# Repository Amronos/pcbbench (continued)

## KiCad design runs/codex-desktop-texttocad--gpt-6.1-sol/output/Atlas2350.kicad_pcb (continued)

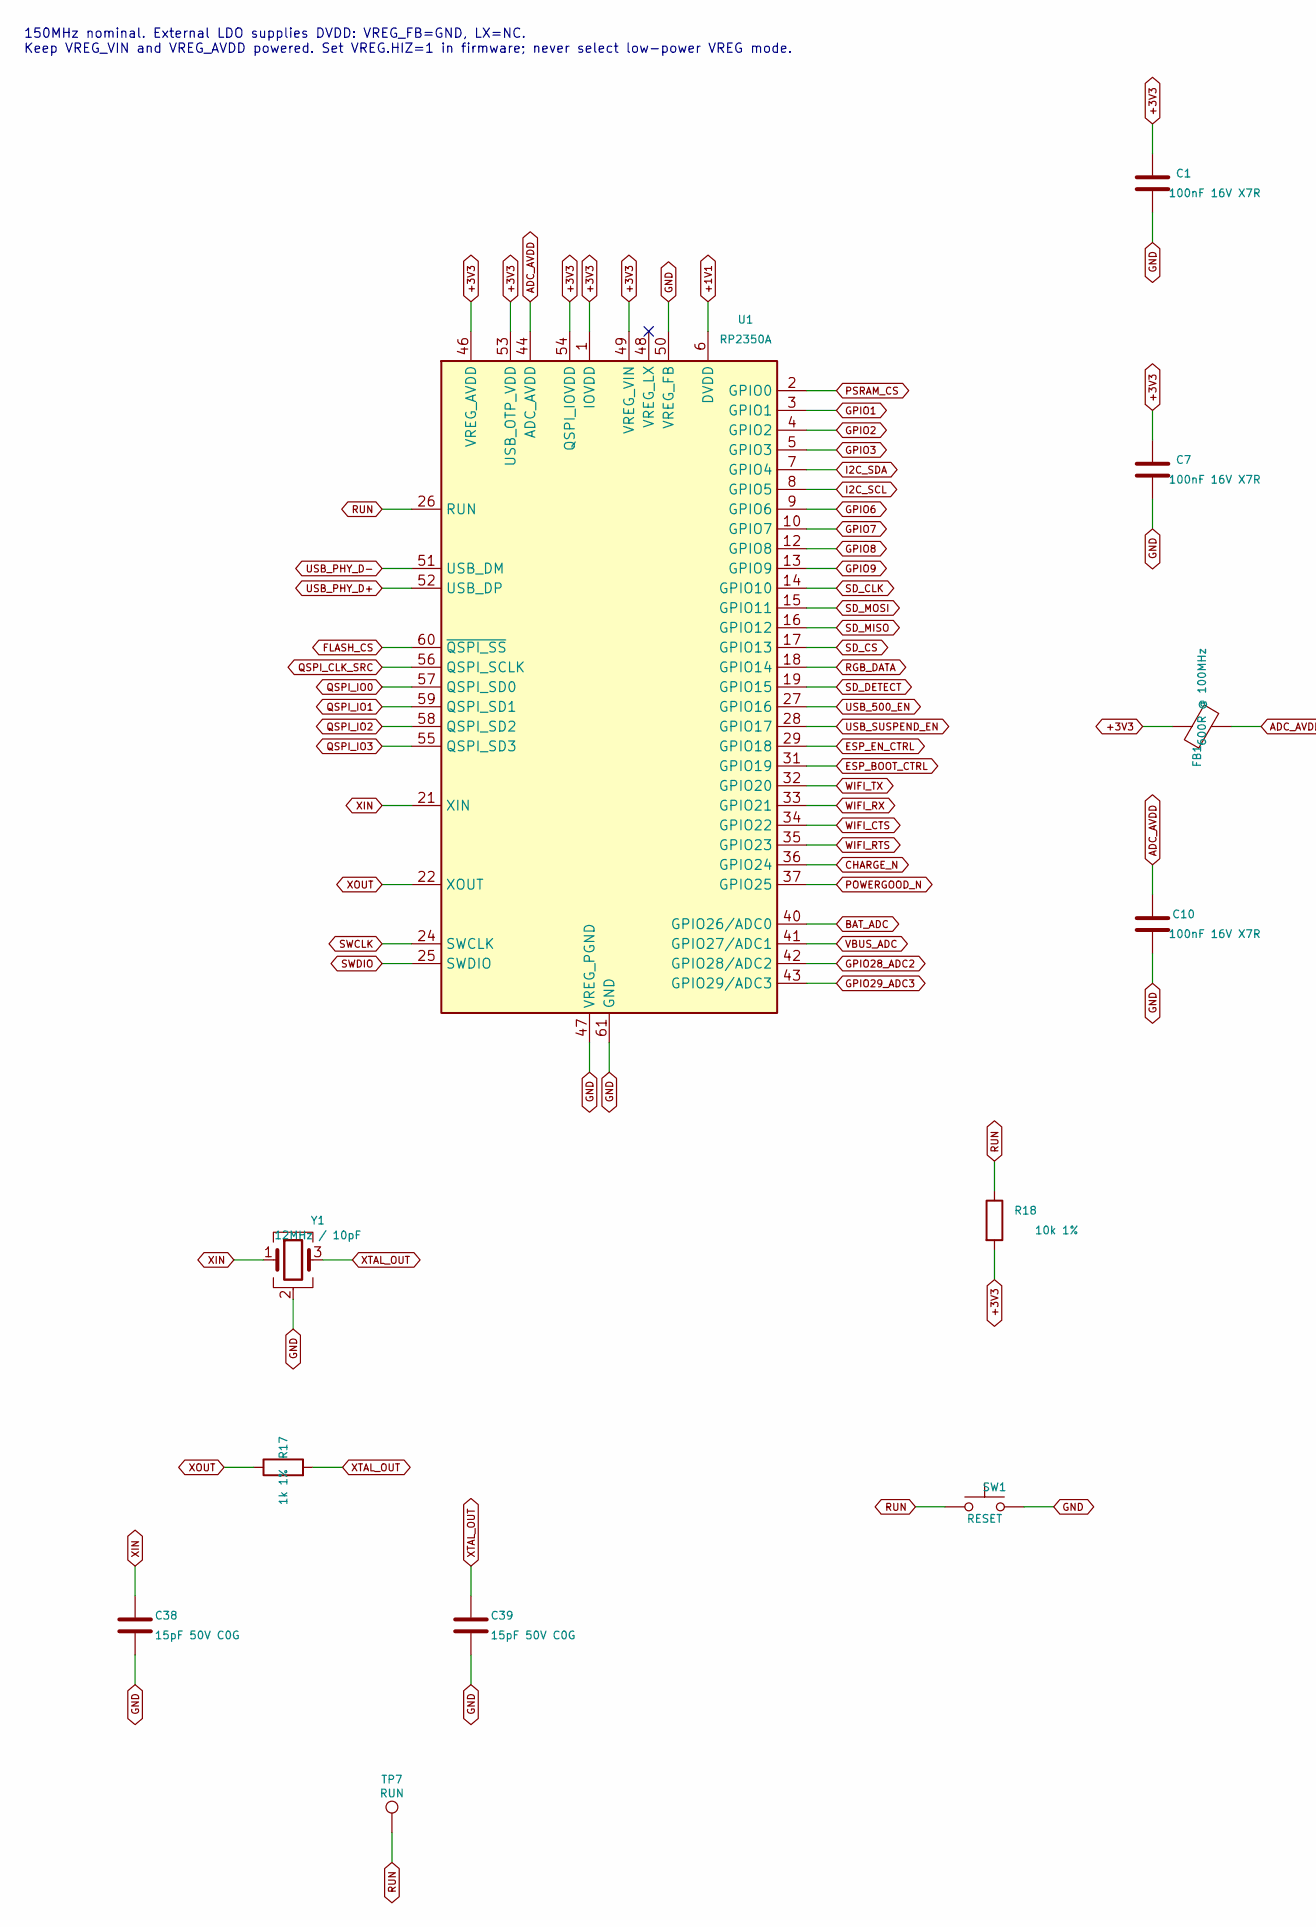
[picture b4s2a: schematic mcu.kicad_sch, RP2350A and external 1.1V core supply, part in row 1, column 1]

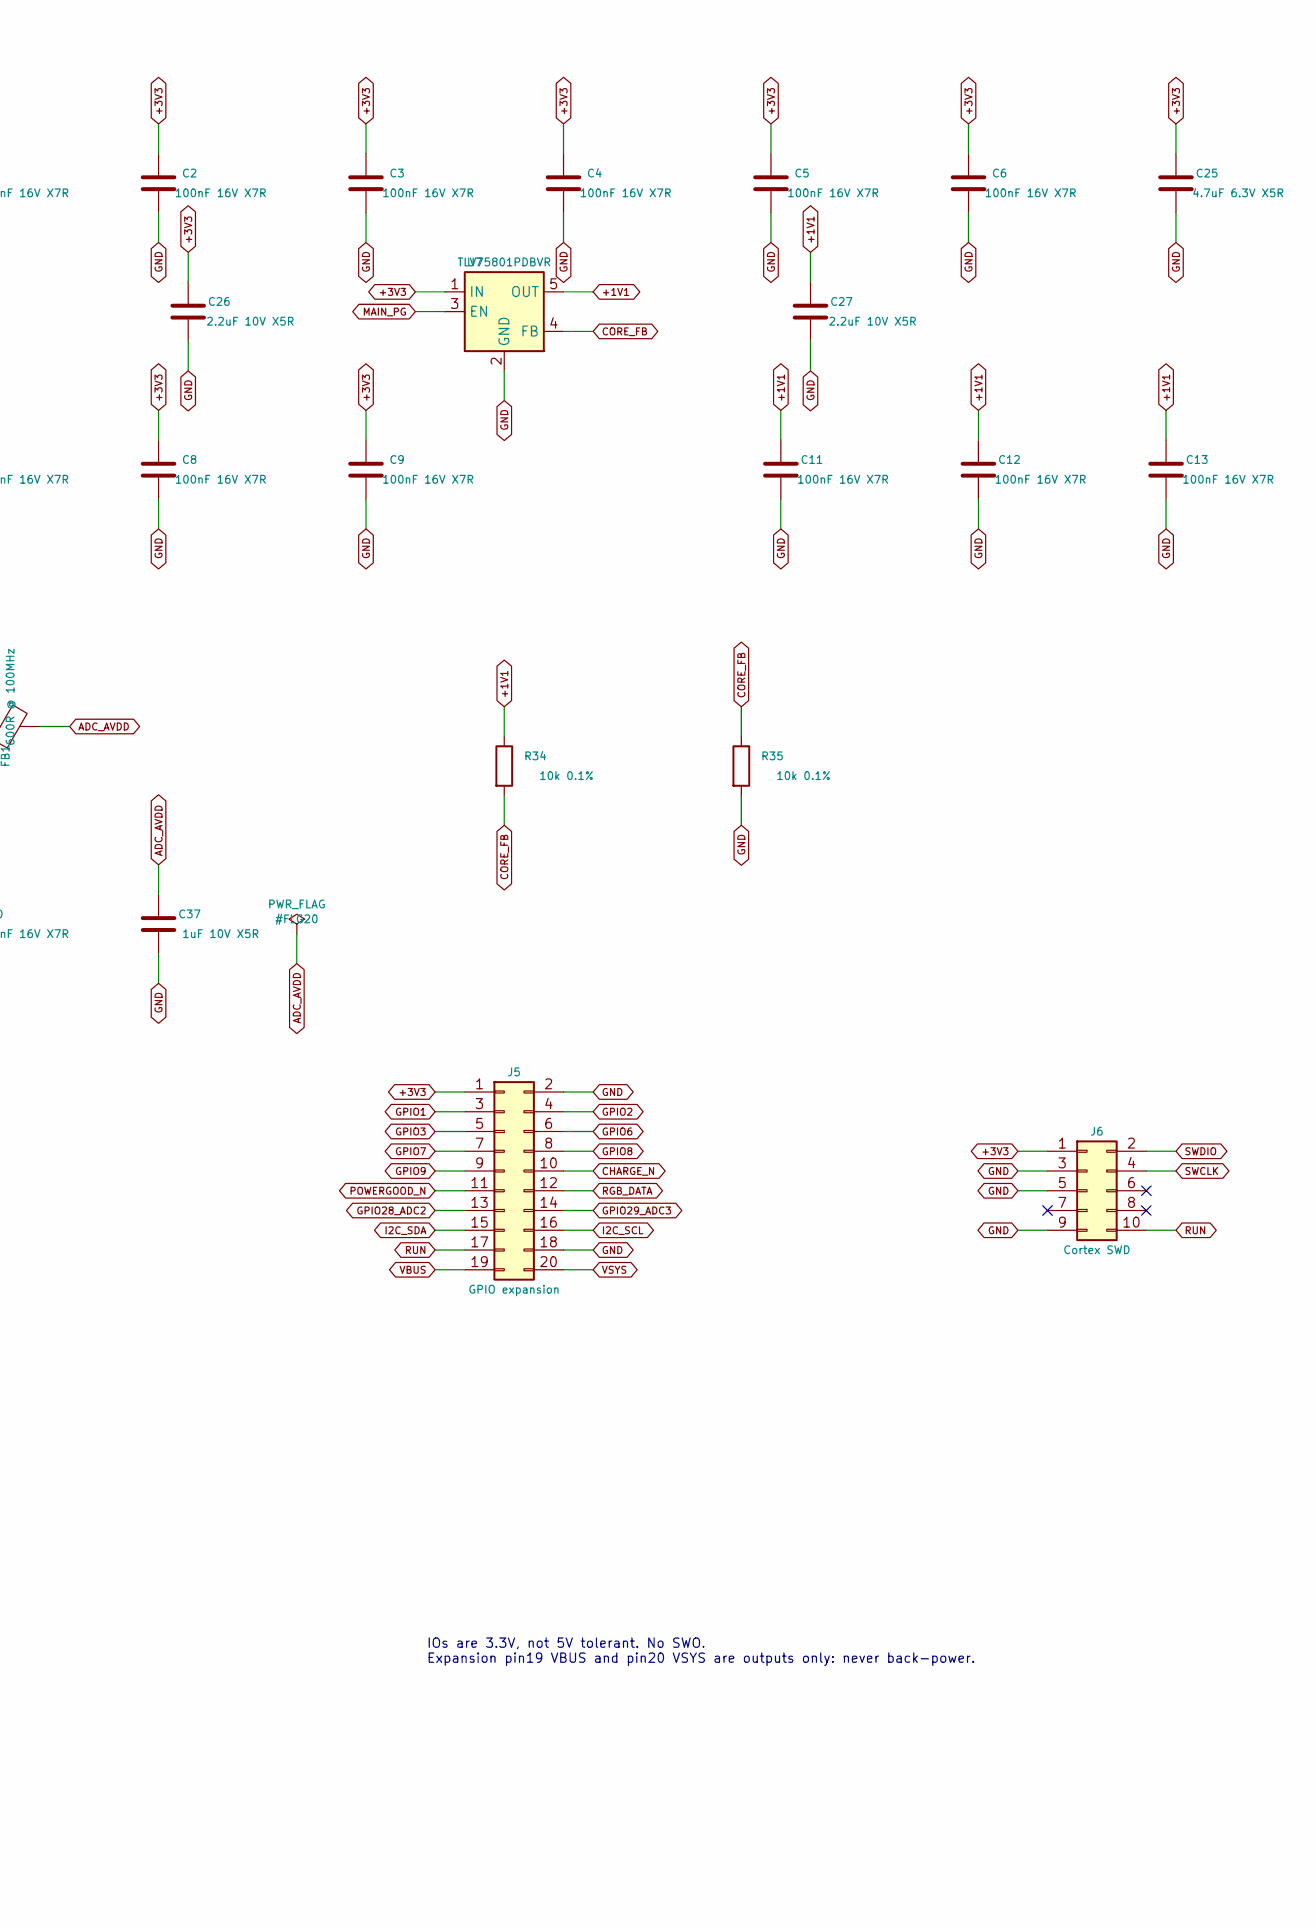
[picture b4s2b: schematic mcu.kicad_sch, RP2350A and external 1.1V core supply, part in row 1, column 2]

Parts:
C1, C2, C3, C4, C5, C6, C7, C8, C9, C10, C11, C12, C13: 100nF 16V X7R; Capacitor_SMD_C_0402_1005Metric; MPN GRM155R71C104KA88D
C25: 4.7uF 6.3V X5R; Capacitor_SMD_C_0603_1608Metric; MPN GRM188R60J475KE19D
C26, C27: 2.2uF 10V X5R; Capacitor_SMD_C_0603_1608Metric; MPN GRM188R61A225KE15D
C37: 1uF 10V X5R; Capacitor_SMD_C_0402_1005Metric; MPN GRM155R61A105KE15D
C38, C39: 15pF 50V C0G; Capacitor_SMD_C_0402_1005Metric; MPN GRM1555C1H150JA01D
FB1: 600R @ 100MHz; Inductor_SMD_L_0402_1005Metric; MPN BLM15AG601SN1D
J5: GPIO expansion; Connector_PinHeader_2.54mm_PinHeader_2x10_P2.54mm_Vertical; MPN TSW-110-07-G-D
J6: Cortex SWD; Connector_PinHeader_1.27mm_PinHeader_2x05_P1.27mm_Vertical; MPN FTSH-105-01-L-D
R17: 1k 1%; Resistor_SMD_R_0402_1005Metric; MPN RC0402FR-071KL
R18: 10k 1%; Resistor_SMD_R_0402_1005Metric; MPN RC0402FR-0710KL
R34, R35: 10k 0.1%; Resistor_SMD_R_0402_1005Metric; MPN RT0402BRD0710KL
SW1: RESET; Button_Switch_SMD_SW_SPST_TL3342; MPN TL3342F160QG
TP7: RUN; TestPoint_TestPoint_Pad_D1.0mm
U1: RP2350A; Package_DFN_QFN_QFN-60-1EP_7x7mm_P0.4mm_EP3.4x3.4mm; MPN RP2350A
U7: TLV75801PDBVR; Package_TO_SOT_SMD_SOT-23-5; MPN TLV75801PDBVR
Y1: 12MHz / 10pF; Crystal_Crystal_SMD_Abracon_ABM8G-4Pin_3.2x2.5mm; MPN ABM8-272-T3

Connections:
+1V1: C11.1, C12.1, C13.1, C27.1, R34.1, U1.6 (DVDD), U1.23 (DVDD), U1.39 (DVDD), U7.5 (OUT); also elsewhere on the board
+3V3: C1.1, C2.1, C3.1, C4.1, C5.1, C6.1, C7.1, C8.1, C9.1, C25.1, C26.1, FB1.1, J5.1, J6.1, R18.2, U1.1 (IOVDD), U1.11 (IOVDD), U1.20 (IOVDD), U1.30 (IOVDD), U1.38 (IOVDD), U1.45 (IOVDD), U1.46 (VREG_AVDD), U1.49 (VREG_VIN), U1.53 (USB_OTP_VDD), U1.54 (QSPI_IOVDD), U7.1 (IN); also elsewhere on the board
ADC_AVDD: C10.1, C37.1, FB1.2, U1.44 (ADC_AVDD)
BAT_ADC: U1.40 (GPIO26/ADC0); also elsewhere on the board
CHARGE_N: J5.10, U1.36 (GPIO24); also elsewhere on the board
CORE_FB: R34.2, R35.1, U7.4 (FB)
ESP_BOOT_CTRL: U1.31 (GPIO19); also elsewhere on the board
ESP_EN_CTRL: U1.29 (GPIO18); also elsewhere on the board
FLASH_CS: U1.60 (~QSPI_SS); also elsewhere on the board
GND: C1.2, C2.2, C3.2, C4.2, C5.2, C6.2, C7.2, C8.2, C9.2, C10.2, C11.2, C12.2, C13.2, C25.2, C26.2, C27.2, C37.2, C38.2, C39.2, J5.2, J5.18, J6.3, J6.5, J6.9, R35.2, SW1.2, U1.47 (VREG_PGND), U1.50 (VREG_FB), U1.61 (GND), U7.2 (GND), Y1.2 (G), Y1.4 (G); also elsewhere on the board
GPIO1: J5.3, U1.3 (GPIO1)
GPIO2: J5.4, U1.4 (GPIO2)
GPIO3: J5.5, U1.5 (GPIO3)
GPIO6: J5.6, U1.9 (GPIO6)
GPIO7: J5.7, U1.10 (GPIO7)
GPIO8: J5.8, U1.12 (GPIO8)
GPIO9: J5.9, U1.13 (GPIO9)
GPIO28_ADC2: J5.13, U1.42 (GPIO28/ADC2)
GPIO29_ADC3: J5.14, U1.43 (GPIO29/ADC3)
I2C_SCL: J5.16, U1.8 (GPIO5); also elsewhere on the board
I2C_SDA: J5.15, U1.7 (GPIO4); also elsewhere on the board
MAIN_PG: U7.3 (EN); also elsewhere on the board
POWERGOOD_N: J5.11, U1.37 (GPIO25); also elsewhere on the board
PSRAM_CS: U1.2 (GPIO0); also elsewhere on the board
QSPI_CLK_SRC: U1.56 (QSPI_SCLK); also elsewhere on the board
QSPI_IO0: U1.57 (QSPI_SD0); also elsewhere on the board
QSPI_IO1: U1.59 (QSPI_SD1); also elsewhere on the board
QSPI_IO2: U1.58 (QSPI_SD2); also elsewhere on the board
QSPI_IO3: U1.55 (QSPI_SD3); also elsewhere on the board
RGB_DATA: J5.12, U1.18 (GPIO14); also elsewhere on the board
RUN: J5.17, J6.10, R18.1, SW1.1, TP7.1 (1_1), U1.26 (RUN)
SD_CLK: U1.14 (GPIO10); also elsewhere on the board
SD_CS: U1.17 (GPIO13); also elsewhere on the board
SD_DETECT: U1.19 (GPIO15); also elsewhere on the board
SD_MISO: U1.16 (GPIO12); also elsewhere on the board
SD_MOSI: U1.15 (GPIO11); also elsewhere on the board
SWCLK: J6.4, U1.24 (SWCLK)
SWDIO: J6.2, U1.25 (SWDIO)
USB_500_EN: U1.27 (GPIO16); also elsewhere on the board
USB_PHY_D+: U1.52 (USB_DP); also elsewhere on the board
USB_PHY_D-: U1.51 (USB_DM); also elsewhere on the board
USB_SUSPEND_EN: U1.28 (GPIO17); also elsewhere on the board
VBUS: J5.19; also elsewhere on the board
VBUS_ADC: U1.41 (GPIO27/ADC1); also elsewhere on the board
VSYS: J5.20; also elsewhere on the board
WIFI_CTS: U1.34 (GPIO22); also elsewhere on the board
WIFI_RTS: U1.35 (GPIO23); also elsewhere on the board
WIFI_RX: U1.33 (GPIO21); also elsewhere on the board
WIFI_TX: U1.32 (GPIO20); also elsewhere on the board
XIN: C38.1, U1.21 (XIN), Y1.1
XOUT: R17.1, U1.22 (XOUT)
XTAL_OUT: C39.1, R17.2, Y1.3

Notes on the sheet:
150MHz nominal. External LDO supplies DVDD: VREG_FB=GND, LX=NC. Keep VREG_VIN and VREG_AVDD powered. Set VREG.HIZ=1 in firmware; never select low-power VREG mode.
IOs are 3.3V, not 5V tolerant. No SWO. Expansion pin19 VBUS and pin20 VSYS are outputs only: never back-power.

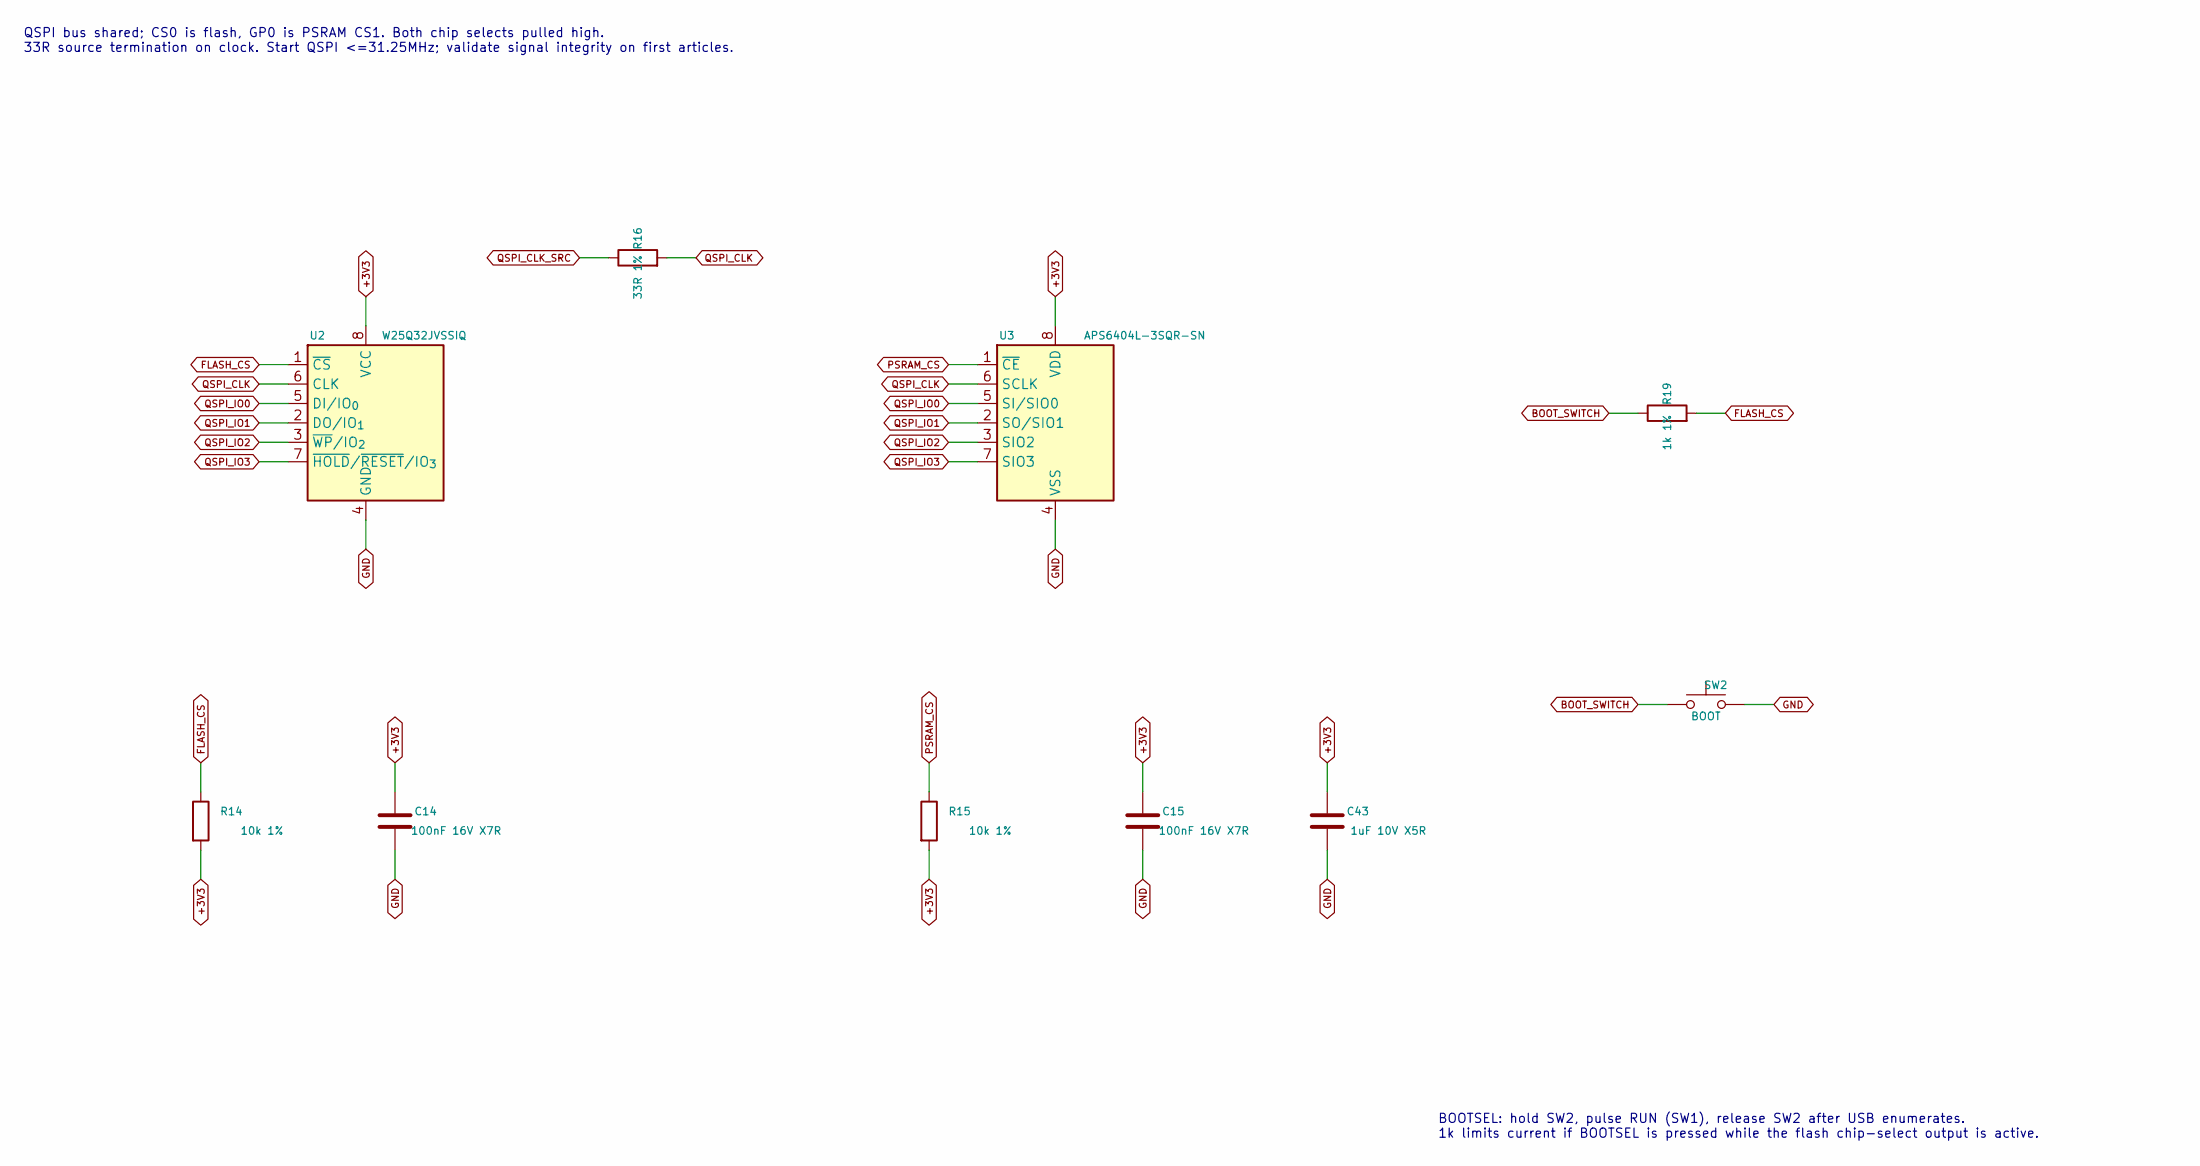
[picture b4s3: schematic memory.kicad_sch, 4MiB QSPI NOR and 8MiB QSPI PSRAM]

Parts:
C14, C15: 100nF 16V X7R; Capacitor_SMD_C_0402_1005Metric; MPN GRM155R71C104KA88D
C43: 1uF 10V X5R; Capacitor_SMD_C_0402_1005Metric; MPN GRM155R61A105KE15D
R14, R15: 10k 1%; Resistor_SMD_R_0402_1005Metric; MPN RC0402FR-0710KL
R16: 33R 1%; Resistor_SMD_R_0402_1005Metric; MPN RC0402FR-0733RL
R19: 1k 1%; Resistor_SMD_R_0402_1005Metric; MPN RC0402FR-071KL
SW2: BOOT; Button_Switch_SMD_SW_SPST_TL3342; MPN TL3342F160QG
U2: W25Q32JVSSIQ; Package_SO_SOIC-8_5.3x5.3mm_P1.27mm; MPN W25Q32JVSSIQ
U3: APS6404L-3SQR-SN; Package_SO_SOIC-8_3.9x4.9mm_P1.27mm; MPN APS6404L-3SQR-SN

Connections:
+3V3: C14.1, C15.1, C43.1, R14.2, R15.2, U2.8 (VCC), U3.8 (VDD); also elsewhere on the board
BOOT_SWITCH: R19.1, SW2.1
FLASH_CS: R14.1, R19.2, U2.1 (~CS); also elsewhere on the board
GND: C14.2, C15.2, C43.2, SW2.2, U2.4 (GND), U3.4 (VSS); also elsewhere on the board
PSRAM_CS: R15.1, U3.1 (~CE); also elsewhere on the board
QSPI_CLK: R16.2, U2.6 (CLK), U3.6 (SCLK)
QSPI_CLK_SRC: R16.1; also elsewhere on the board
QSPI_IO0: U2.5 (DI/IO_{0}), U3.5 (SI/SIO0); also elsewhere on the board
QSPI_IO1: U2.2 (DO/IO_{1}), U3.2 (SO/SIO1); also elsewhere on the board
QSPI_IO2: U2.3 (~WP/IO_{2}), U3.3 (SIO2); also elsewhere on the board
QSPI_IO3: U2.7 (~HOLD/~RESET/IO_{3}), U3.7 (SIO3); also elsewhere on the board

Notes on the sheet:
QSPI bus shared; CS0 is flash, GP0 is PSRAM CS1. Both chip selects pulled high. 33R source termination on clock. Start QSPI <=31.25MHz; validate signal integrity on first articles.
BOOTSEL: hold SW2, pulse RUN (SW1), release SW2 after USB enumerates. 1k limits current if BOOTSEL is pressed while the flash chip-select output is active.

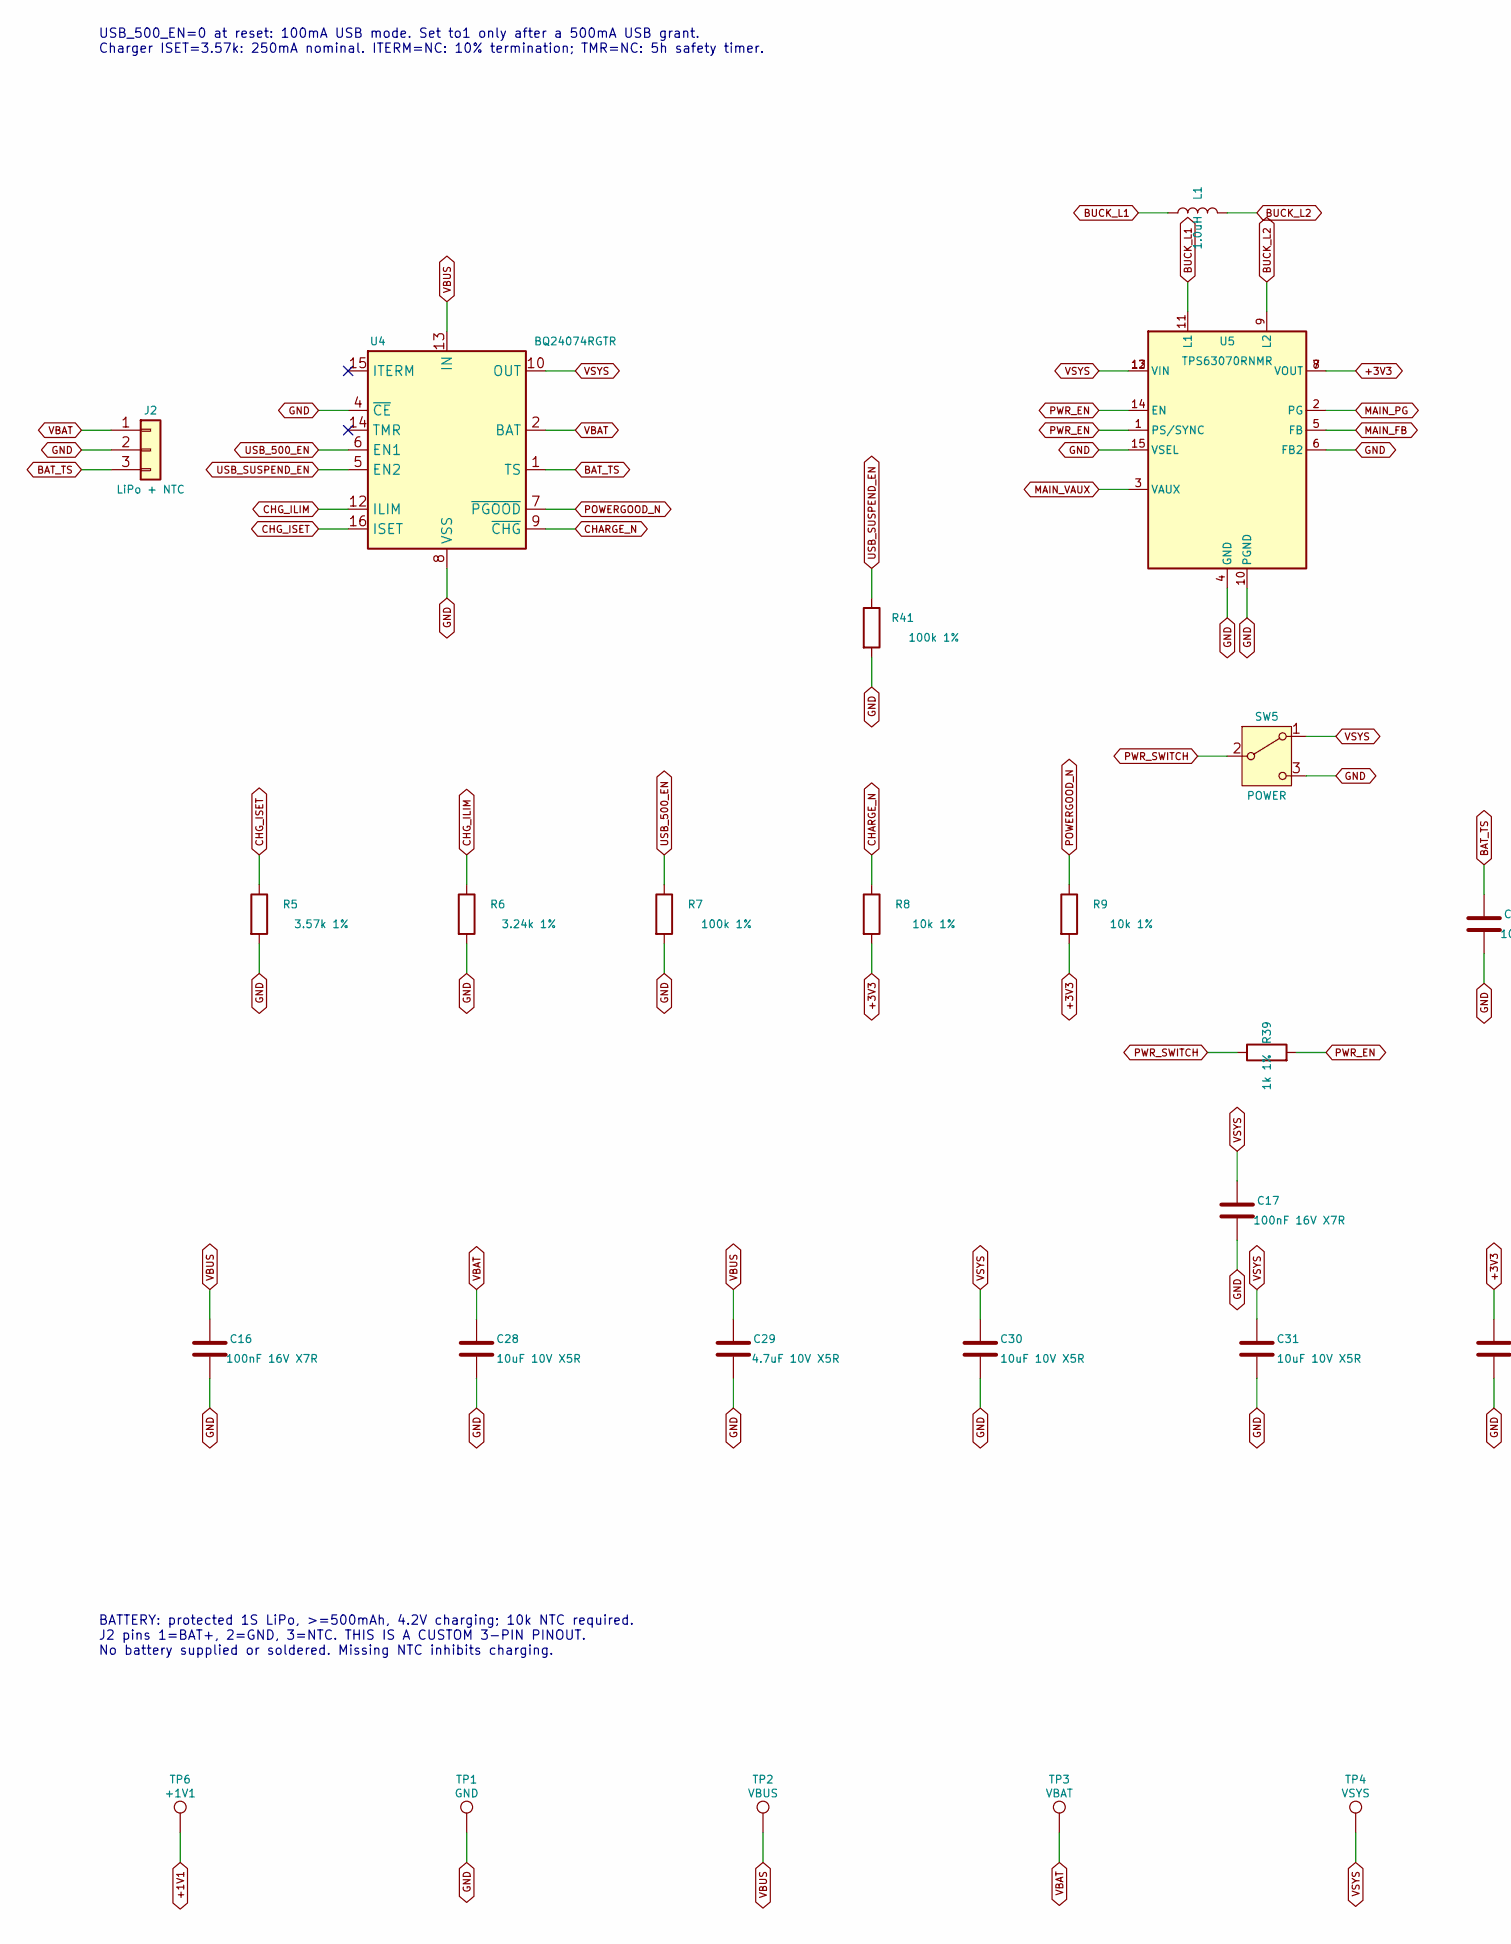
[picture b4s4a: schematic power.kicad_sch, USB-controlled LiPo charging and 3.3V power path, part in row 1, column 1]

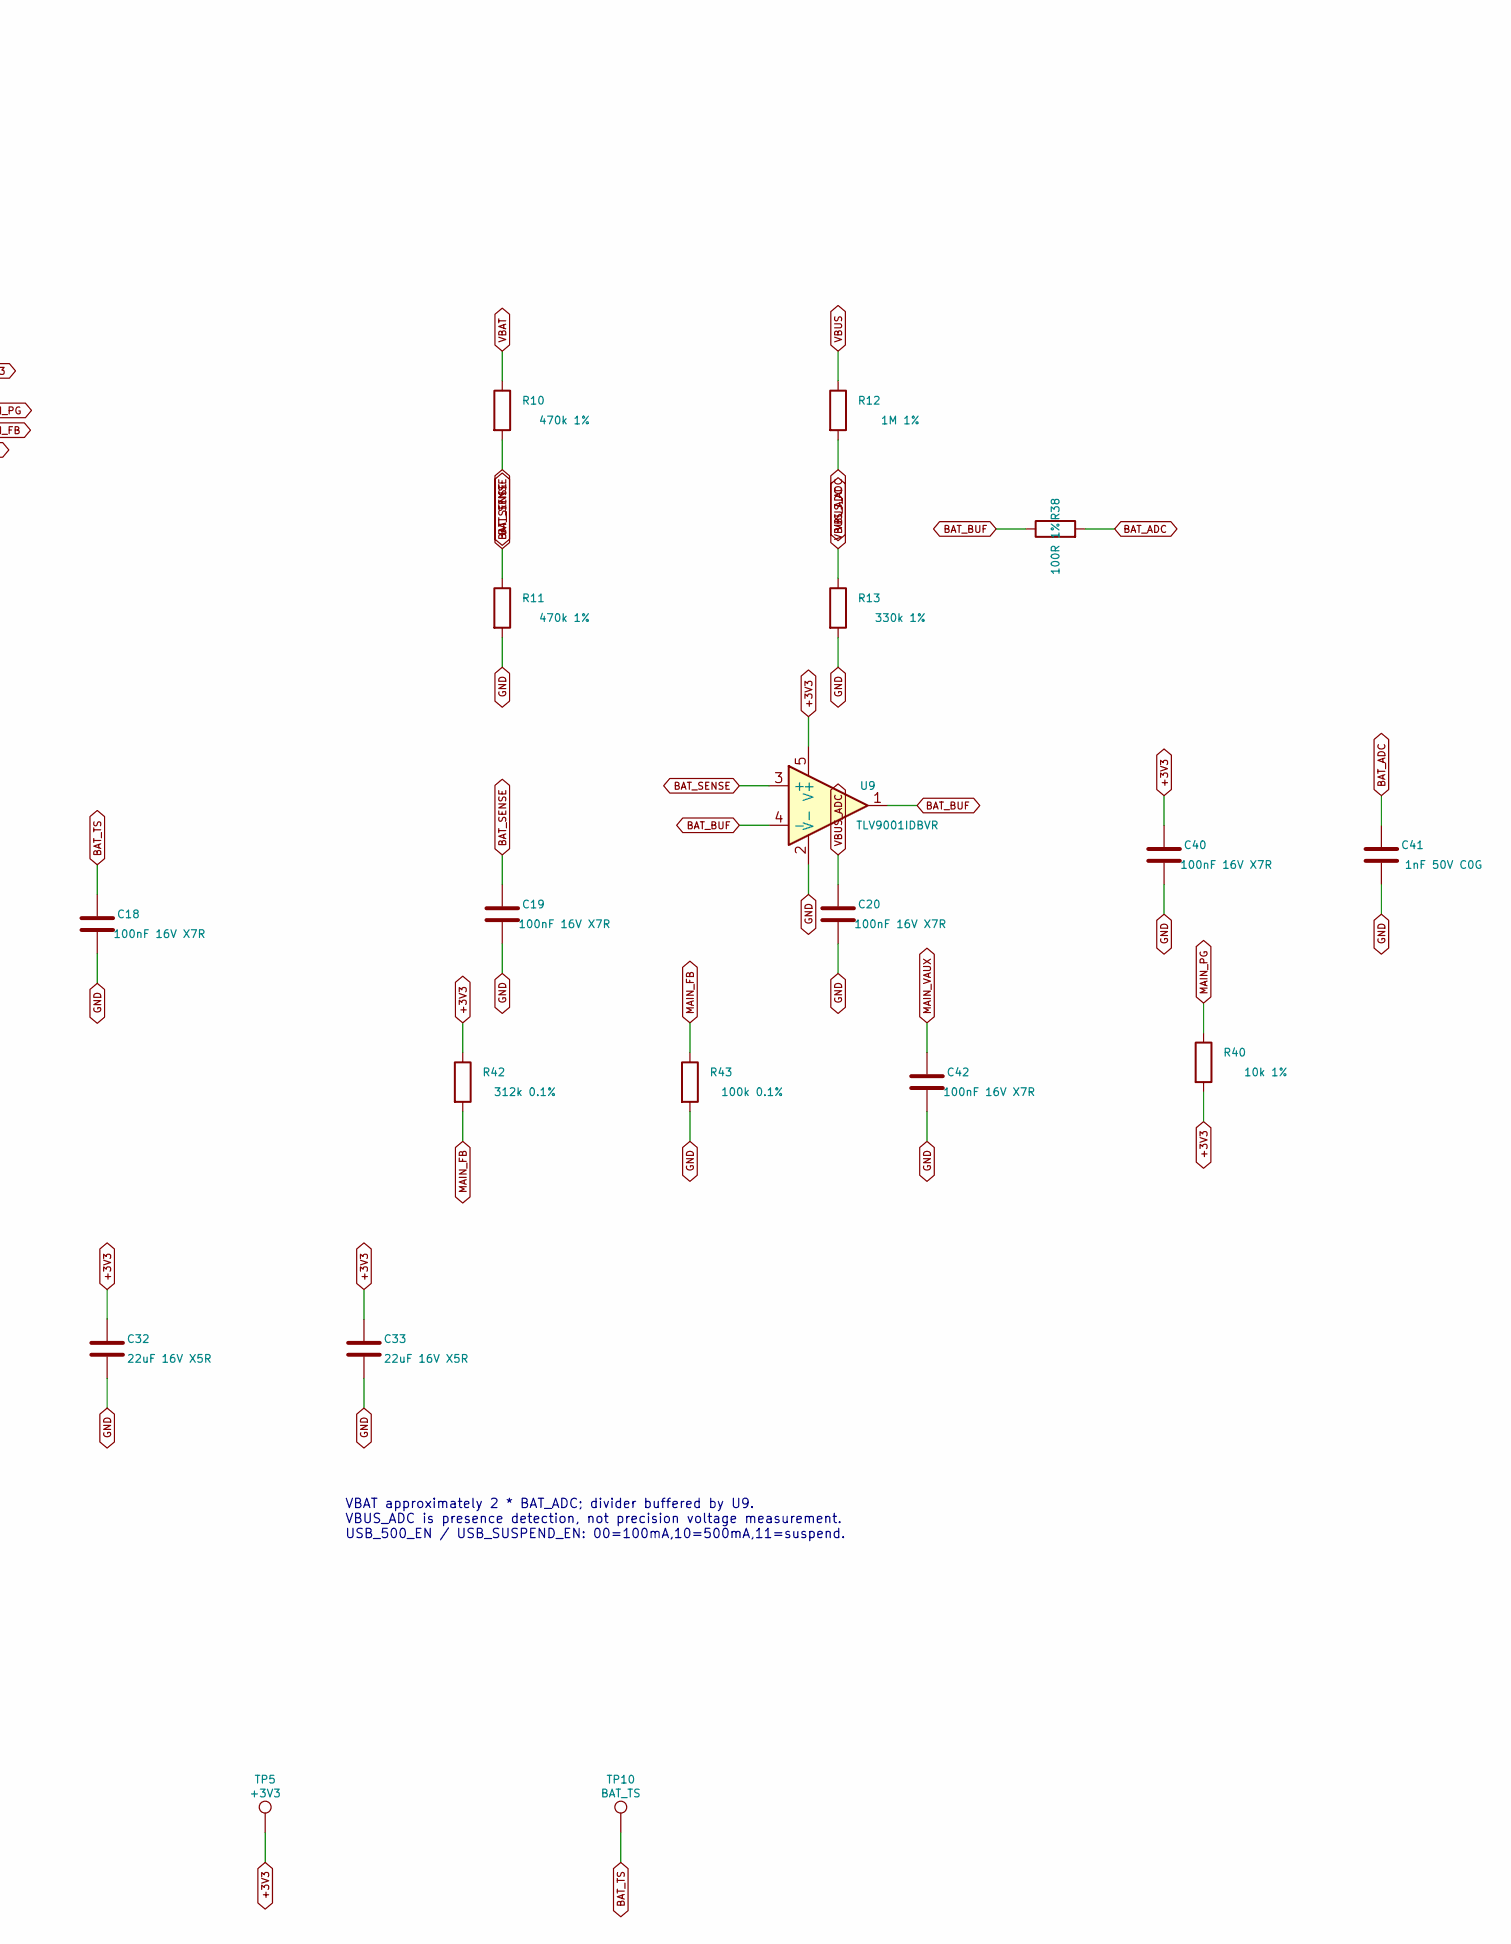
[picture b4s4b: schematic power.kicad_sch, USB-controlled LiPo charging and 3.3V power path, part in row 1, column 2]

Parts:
C16, C17, C18, C19, C20, C40, C42: 100nF 16V X7R; Capacitor_SMD_C_0402_1005Metric; MPN GRM155R71C104KA88D
C28, C30, C31: 10uF 10V X5R; Capacitor_SMD_C_0805_2012Metric; MPN GRM21BR61A106KE19L
C29: 4.7uF 10V X5R; Capacitor_SMD_C_0805_2012Metric; MPN GRM21BR61A475KA73L
C32, C33: 22uF 16V X5R; Capacitor_SMD_C_1206_3216Metric; MPN GRM31CR61C226KE15L
C41: 1nF 50V C0G; Capacitor_SMD_C_0402_1005Metric; MPN GRM1555C1H102JA01D
J2: LiPo + NTC; Connector_JST_JST_PH_S3B-PH-SM4-TB_1x03-1MP_P2.00mm_Horizon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; MPN S3B-PH-SM4-TB(LF)(SN)
L1: 1.0uH; Inductor_SMD_L_Coilcraft_XAL4020-XXX; MPN XAL4020-102MEC
R5: 3.57k 1%; Resistor_SMD_R_0402_1005Metric; MPN RC0402FR-073K57L
R6: 3.24k 1%; Resistor_SMD_R_0402_1005Metric; MPN RC0402FR-073K24L
R7, R41: 100k 1%; Resistor_SMD_R_0402_1005Metric; MPN RC0402FR-07100KL
R8, R9, R40: 10k 1%; Resistor_SMD_R_0402_1005Metric; MPN RC0402FR-0710KL
R10, R11: 470k 1%; Resistor_SMD_R_0402_1005Metric; MPN RC0402FR-07470KL
R12: 1M 1%; Resistor_SMD_R_0402_1005Metric; MPN RC0402FR-071ML
R13: 330k 1%; Resistor_SMD_R_0402_1005Metric; MPN RC0402FR-07330KL
R38: 100R 1%; Resistor_SMD_R_0402_1005Metric; MPN RC0402FR-07100RL
R39: 1k 1%; Resistor_SMD_R_0402_1005Metric; MPN RC0402FR-071KL
R42: 312k 0.1%; Resistor_SMD_R_0402_1005Metric; MPN RT0402BRD07312KL
R43: 100k 0.1%; Resistor_SMD_R_0402_1005Metric; MPN RT0402BRD07100KL
SW5: POWER; Button_Switch_SMD_SW_SPDT_CK_JS102011SAQN; MPN JS102011SAQN
TP1: GND; TestPoint_TestPoint_Pad_D1.0mm
TP2: VBUS; TestPoint_TestPoint_Pad_D1.0mm
TP3: VBAT; TestPoint_TestPoint_Pad_D1.0mm
TP4: VSYS; TestPoint_TestPoint_Pad_D1.0mm
TP5: +3V3; TestPoint_TestPoint_Pad_D1.0mm
TP6: +1V1; TestPoint_TestPoint_Pad_D1.0mm
TP10: BAT_TS; TestPoint_TestPoint_Pad_D1.0mm
U4: BQ24074RGTR; Package_DFN_QFN_VQFN-16-1EP_3x3mm_P0.5mm_EP1.6x1.6mm; MPN BQ24074RGTR
U5: TPS63070RNMR; Custom_TPS63070_RNM0015A; MPN TPS63070RNMR
U9: TLV9001IDBVR; Package_TO_SOT_SMD_SOT-23-5; MPN TLV9001IDBVR

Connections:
+1V1: TP6.1 (1_1); also elsewhere on the board
+3V3: C32.1, C33.1, C40.1, R8.2, R9.2, R40.2, R42.1, TP5.1 (1_1), U5.7 (VOUT), U5.8 (VOUT), U9.5 (V+); also elsewhere on the board
BAT_ADC: C41.1, R38.2; also elsewhere on the board
BAT_BUF: R38.1, U9.1, U9.4 (-)
BAT_SENSE: C19.1, R10.2, R11.1, U9.3 (+)
BAT_TS: C18.1, J2.3, TP10.1 (1_1), U4.1 (TS)
BUCK_L1: L1.1, U5.11 (L1)
BUCK_L2: L1.2, U5.9 (L2)
CHARGE_N: R8.1, U4.9 (~CHG); also elsewhere on the board
CHG_ILIM: R6.1, U4.12 (ILIM)
CHG_ISET: R5.1, U4.16 (ISET)
GND: C16.2, C17.2, C18.2, C19.2, C20.2, C28.2, C29.2, C30.2, C31.2, C32.2, C33.2, C40.2, C41.2, C42.2, J2.2, R5.2, R6.2, R7.2, R11.2, R13.2, R41.2, R43.2, SW5.3 (C), TP1.1 (1_1), U4.4 (~CE), U4.8 (VSS), U4.17 (VSS), U5.4 (GND), U5.6 (FB2), U5.10 (PGND), U5.15 (VSEL), U9.2 (V-); also elsewhere on the board
MAIN_FB: R42.2, R43.1, U5.5 (FB)
MAIN_PG: R40.1, U5.2 (PG); also elsewhere on the board
MAIN_VAUX: C42.1, U5.3 (VAUX)
POWERGOOD_N: R9.1, U4.7 (~PGOOD); also elsewhere on the board
PWR_EN: R39.2, U5.1 (PS/SYNC), U5.14 (EN); also elsewhere on the board
PWR_SWITCH: R39.1, SW5.2 (B)
USB_500_EN: R7.1, U4.6 (EN1); also elsewhere on the board
USB_SUSPEND_EN: R41.1, U4.5 (EN2); also elsewhere on the board
VBAT: C28.1, J2.1, R10.1, TP3.1 (1_1), U4.2 (BAT), U4.3 (BAT)
VBUS: C16.1, C29.1, R12.1, TP2.1 (1_1), U4.13 (IN); also elsewhere on the board
VBUS_ADC: C20.1, R12.2, R13.1; also elsewhere on the board
VSYS: C17.1, C30.1, C31.1, SW5.1 (A), TP4.1 (1_1), U4.10 (OUT), U4.11 (OUT), U5.12 (VIN), U5.13 (VIN); also elsewhere on the board

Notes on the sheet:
USB_500_EN=0 at reset: 100mA USB mode. Set to1 only after a 500mA USB grant. Charger ISET=3.57k: 250mA nominal. ITERM=NC: 10% termination; TMR=NC: 5h safety timer.
BATTERY: protected 1S LiPo, >=500mAh, 4.2V charging; 10k NTC required. J2 pins 1=BAT+, 2=GND, 3=NTC. THIS IS A CUSTOM 3-PIN PINOUT. No battery supplied or soldered. Missing NTC inhibits charging.
VBAT approximately 2 * BAT_ADC; divider buffered by U9. VBUS_ADC is presence detection, not precision voltage measurement. USB_500_EN / USB_SUSPEND_EN: 00=100mA,10=500mA,11=suspend.
